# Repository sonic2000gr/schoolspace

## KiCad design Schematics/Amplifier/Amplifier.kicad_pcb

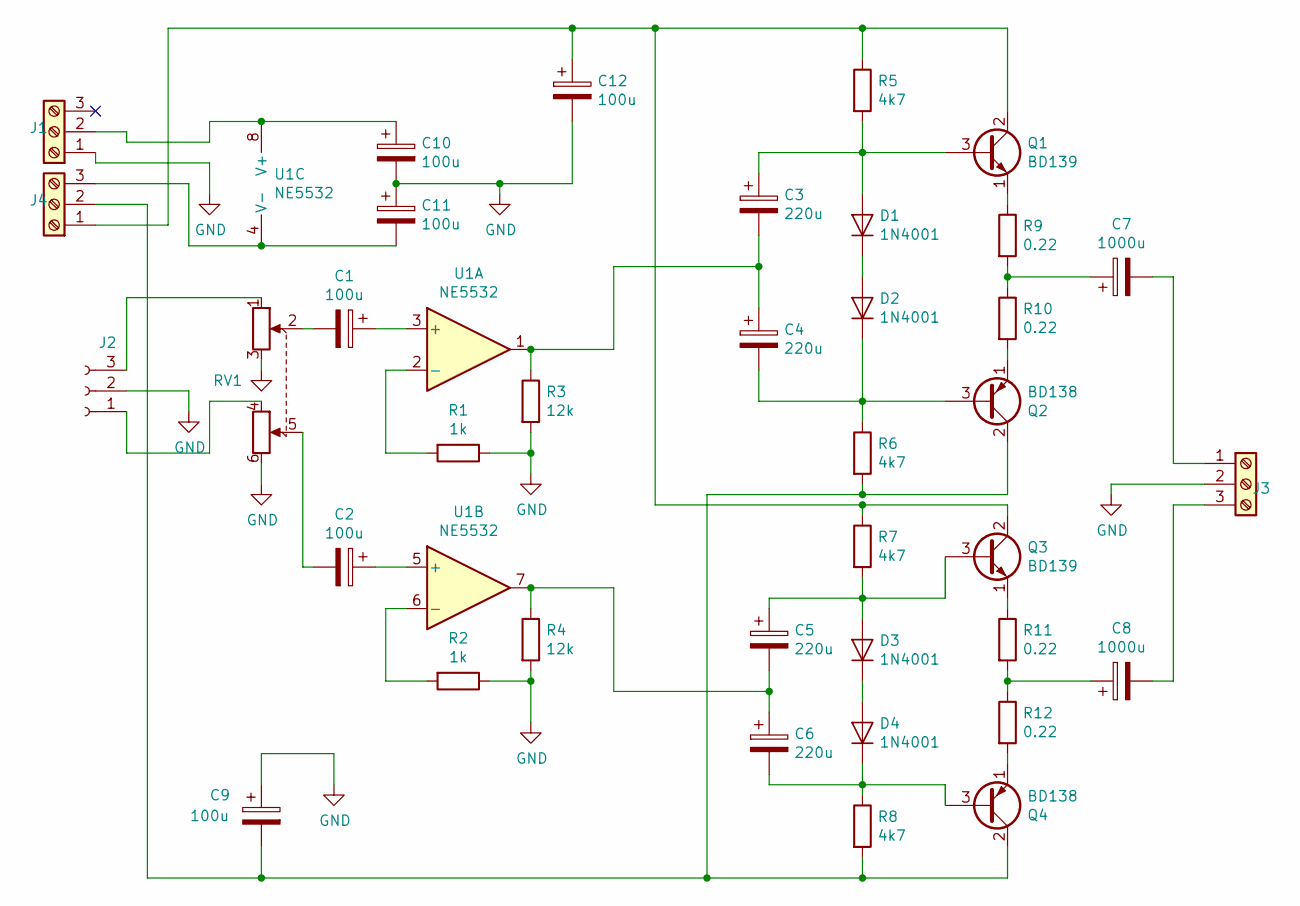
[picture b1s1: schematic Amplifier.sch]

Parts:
C1, C2, C9, C10, C11, C12: 100u; C_Radial_D10.0mm_H12.5mm_P5.00mm
C3, C4, C5, C6: 220u; C_Radial_D10.0mm_H12.5mm_P5.00mm
C7: 1000u; C_Radial_D10.0mm_H12.5mm_P5.00mm
C8: 1000u; C_Radial_D16.0mm_H25.0mm_P7.50mm
D1, D2, D3, D4: 1N4001; D_DO-41_SOD81_P10.16mm_Horizontal
J1, J3, J4: Conn_01x03_Female; TerminalBlock_Altech_AK300-3_P5.00mm
J2: Conn_01x03_Female; PinHeader_1x03_P2.54mm_Vertical
Q1, Q3: BD139; TO-126-3_Vertical
Q2, Q4: BD138; TO-126-3_Vertical
R1, R2: 1k; R_Axial_DIN0204_L3.6mm_D1.6mm_P7.62mm_Horizontal
R3, R4: 12k; R_Axial_DIN0204_L3.6mm_D1.6mm_P7.62mm_Horizontal
R5, R6, R7, R8: 4k7; R_Axial_DIN0204_L3.6mm_D1.6mm_P7.62mm_Horizontal
R9, R10, R11, R12: 0.22; R_Axial_Power_L20.0mm_W6.4mm_P22.40mm
RV1: R_POT_Dual; PinHeader_1x06_P2.54mm_Vertical
U1: NE5532; DIP-8_W7.62mm_LongPads

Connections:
GND: C9.1, C10.2, C11.1, C12.2, J1.1, J2.2, J3.2, R1.1, R2.1, R3.2, R4.2, RV1.3, RV1.6
unnamed: C1.1, U1.3 (+)
unnamed: C1.2, RV1.2
unnamed: C2.1, U1.5 (+)
unnamed: C2.2, RV1.5
unnamed: C3.1, D1.2 (A), Q1.3 (B), R5.2
unnamed: C3.2, C4.1, R3.1, U1.1
unnamed: C4.2, D2.1 (K), Q2.3 (B), R6.1
unnamed: C5.1, D3.2 (A), Q3.3 (B), R7.2
unnamed: C5.2, C6.1, R4.1, U1.7
unnamed: C6.2, D4.1 (K), Q4.3 (B), R8.1
unnamed: C7.1, R9.2, R10.1
unnamed: C7.2, J3.1
unnamed: C8.1, R11.2, R12.1
unnamed: C8.2, J3.3
unnamed: C9.2, J4.2, Q2.2 (C), Q4.2 (C), R6.2, R8.2
unnamed: C10.1, J1.2, U1.8 (V+)
unnamed: C11.2, J4.3, U1.4 (V-)
unnamed: C12.1, J4.1, Q1.2 (C), Q3.2 (C), R5.1, R7.1
unnamed: D1.1 (K), D2.2 (A)
unnamed: D3.1 (K), D4.2 (A)
unnamed: J2.1, RV1.4
unnamed: J2.3, RV1.1
unnamed: Q1.1 (E), R9.1
unnamed: Q2.1 (E), R10.2
unnamed: Q3.1 (E), R11.1
unnamed: Q4.1 (E), R12.2
unnamed: R1.2, U1.2 (-)
unnamed: R2.2, U1.6 (-)

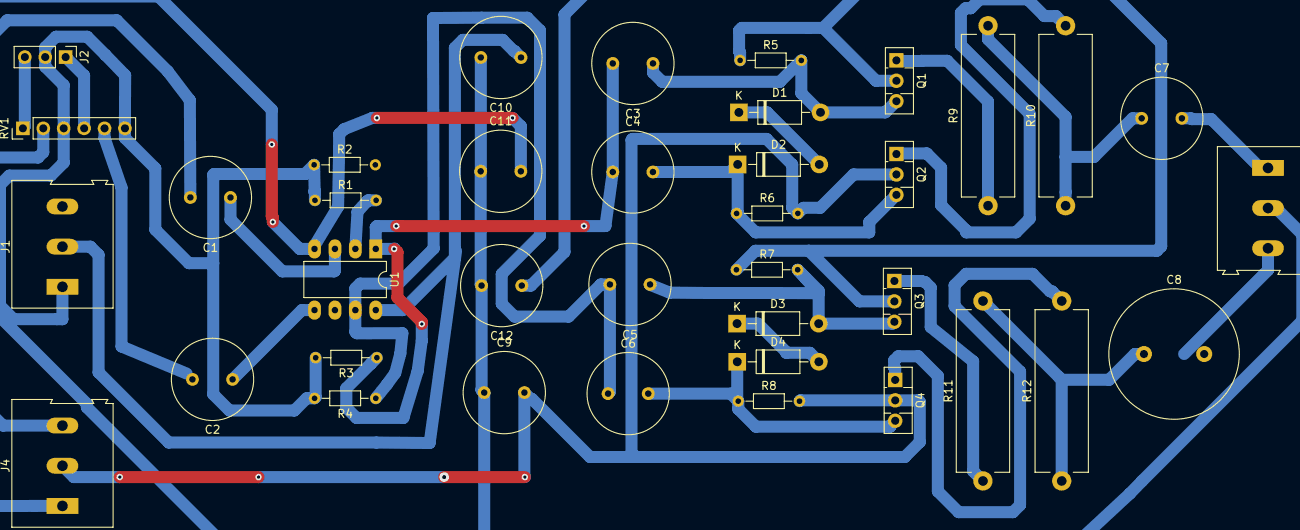
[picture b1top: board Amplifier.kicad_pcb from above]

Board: 2 copper layers, 38 parts (0 on the bottom side), 29 nets.

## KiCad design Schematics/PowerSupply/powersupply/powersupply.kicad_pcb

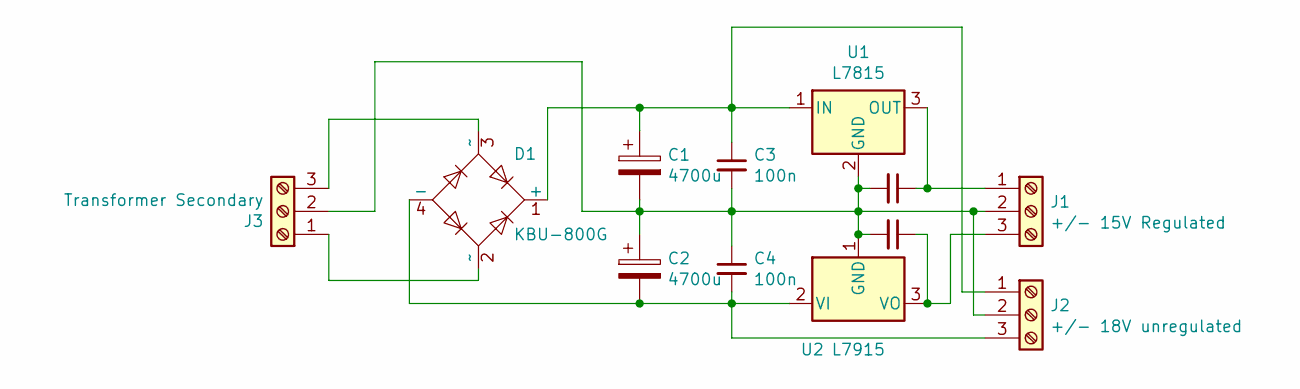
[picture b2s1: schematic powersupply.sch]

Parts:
C1, C2: 4700u; CP_Radial_D17.0mm_P7.50mm
C3, C4: 100n; C_Rect_L9.0mm_W2.5mm_P7.50mm_MKT
C5, C6: C_Small; C_Rect_L9.0mm_W2.5mm_P7.50mm_MKT
D1: KBU-800G; Diode_Bridge_Vishay_KBU
J1: +/- 15V Regulated; TerminalBlock_Altech_AK300-3_P5.00mm
J2: +/- 18V unregulated; TerminalBlock_Altech_AK300-3_P5.00mm
J3: Transformer Secondary; TerminalBlock_Altech_AK300-3_P5.00mm
U1: L7815; TO-220-3_Vertical
U2: L7915; TO-220-3_Vertical

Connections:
unnamed: C1.1, C3.1, D1.1 (+), J2.1, U1.1 (IN)
unnamed: C1.2, C2.1, C3.2, C4.1, C5.2, C6.2, J1.2, J2.2, J3.2, U1.2 (GND), U2.1 (GND)
unnamed: C2.2, C4.2, D1.4 (-), J2.3, U2.2 (VI)
unnamed: C5.1, J1.1, U1.3 (OUT)
unnamed: C6.1, J1.3, U2.3 (VO)
unnamed: D1.2 (~~), J3.1
unnamed: D1.3 (~~), J3.3

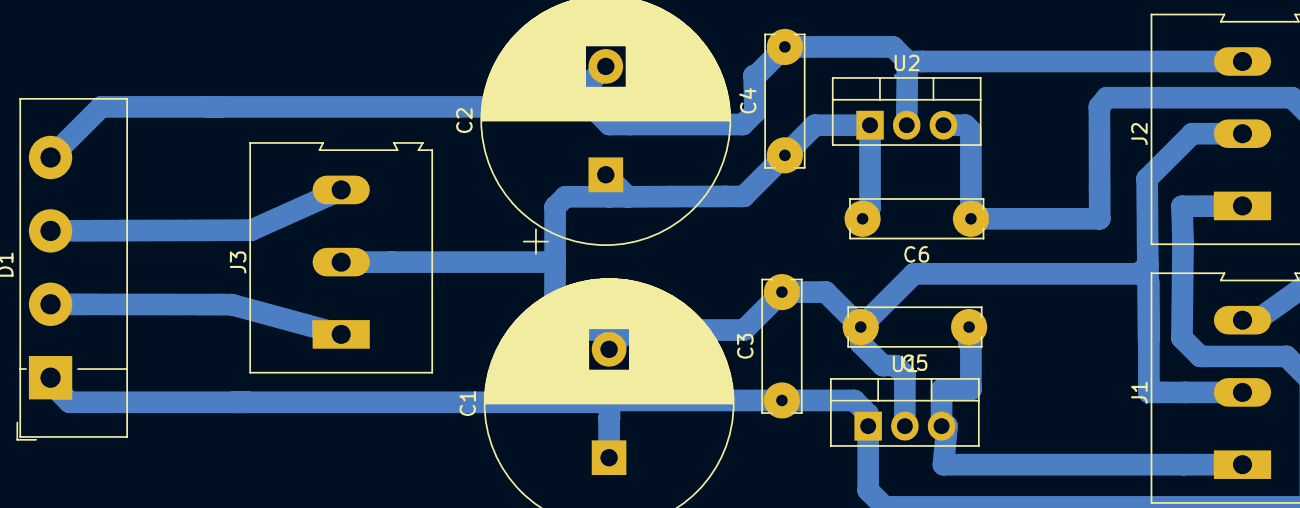
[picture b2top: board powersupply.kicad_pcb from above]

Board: 2 copper layers, 12 parts (0 on the bottom side), 7 nets.

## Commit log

2016-01-19 :space_invader: Added .gitattributes & .gitignore files
2019-03-20 Add initial files for Wind Generator Project
2019-03-21 Modify AC Inverter schematic
2019-04-04 Modify AC invert to use LM386
2019-04-04 Add final version of WindGenerator Arduino sketch
2019-10-23 Add meeting notes
2019-10-23 Add powerpoint / libreoffice presentations
2019-10-23 Add laserchat presentation
2019-10-23 Add battery meter presentation
2019-10-23 Add presentation for Binary system and Arduino
2019-10-29 Add Presentation 01 for 2019 session
2019-10-29 Fix some formulas not formatted correctly
2019-10-29 Fix a few things and add animations
2019-10-30 Change the intro presentation a little bit for 2019
2019-11-01 Add meeting notes for 1st 2019 meeting
2019-11-08 Add presentation for second 2019 session of schoolspace
2019-11-25 Add initial schematic for audio amp (Internet Radio Project)
2019-11-26 Add initial version of Schoolspace presentation 3 for 2019
2019-11-27 Improved presentation 3 for 2019
2019-11-30 Change the slides for the 3rd presentation 2019
2019-12-06 Add notes and presentation for meeting #4
2019-12-13 Add 5th presentation for 2019
2019-12-13 Complete the 5th presentation for 2019
2019-12-16 Add initial version of SonicDuino schematic
2019-12-16 Complete initial version of SonicDuino schematic
2020-01-17 Prepare 6th presentation for 2019
2020-01-17 Add final version of 6th presentation for 2019
2020-01-24 Add 7th presentation for school year 2019-2020
2020-01-25 Add initial schematic for internet radio power supply
2020-02-06 Create PCB for the power supply (amp)
2020-02-07 Add final version of the powersupply pcb
2020-02-11 Add preliminary schematic / pcb for internet Radio Amp
2020-02-12 Continue Amp schematic/PCB
2020-02-14 continuing PCB for amplifier
2020-02-15 Add ninth presentation for 2019-2020
2020-02-18 Update the 8th presentation
2020-02-18 Add some more slides to the 8th presentation
2020-03-06 Add 9th presentation for 2019
2021-11-26 Add first six presentations for 2021-2022
2021-11-27 Adding a second attempt to the amplifier
2021-12-04 Add 7th presentation for Schoolspace 2021, pico python files and modify the previous presentation a bit
2021-12-04 Modify the amp schematic
2021-12-04 Modify the amp schematic a bit (add missing output cap)
2021-12-06 Add christmas for Erasmus project
2021-12-18 Add the 8th presentation for 2021
2021-12-18 Add random.py file
2023-02-04 Presentation for LCD
2023-02-04 Add files for LCD
2023-02-11 Presentation for 11/02/2023
2023-02-11 Pico files for AC/DHT11
2023-02-18 Python program for 28BY-48J stepper motor
2023-02-18 Python file for 28BY-48J stepper motor
2023-02-18 Presentation for 18/02/2023
2023-03-11 Add bridge library
2023-03-11 Add rompotic platform presentations
2024-01-15 Update the presentations to current year (2023-2024)
2024-02-17 Add siren libraries
    Add two siren libaries (two tone, continous)
2025-02-08 Add latest presentations
2025-02-08 Add exhibit presentations
